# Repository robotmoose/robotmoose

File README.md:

# RobotMoose Web Robotics System

This is a simple, modern version of a networked robotics stack, built around the modern web.  The major pieces are:

* A web **front end** for user friendly robot setup, teleoperation, and programming.  See www/js for the code, which is built in JavaScript on bootstrap.
* A central JSON server called **superstar**, used by the robot to make its sensor values available to the front end (as /superstar/*robotname*/sensors), used the by the front end to post robot commands (at /superstar/*robotname*/robots), and used for persistent storage as well.  See superstar/ for the code, which is built in C++ on Mongoose, but the HTTP get and set commands can be sent from any language, and is conceptually similar to MongoDB.
* An on-robot **back end**, that relays superstar commands to the robot hardware, and keeps track of the robot location.  See tabula_rasa/chromeapp for an easy to use RobotMoose chrome app GUI; or tabula_rasa/ for a command line C++ backend.
* A runtime configurable Arduino **firmware**, which allows new robot hardware to be added at runtime without re-flashing or editing the code.

The typical usage model puts the front end on the robot pilot's web browser, superstar on a cloud server accessible from anywhere, the backend on a laptop onboard the robot, and the Arduino directly wired into the robot hardware.  But you can run all the software on a single low-end laptop for a network-free version, or use a dedicated superstar on a closed network, or many other permutations.

## Installation and Setup

To get started with a simulated robot, just visit [robotmoose.com/robots/](https://robotmoose.com/robots/), and click the "Simulate a Robot" button. This will let you get a general sense of how the website works.

### Firmware Installation and Physical Backend

You need [Google Chrome](https://www.google.com/chrome/browser/desktop/index.html) to run the backend, the version control system git to get this code, and the Arduino IDE to flash the Arduino firmware.

Windows:
* [Git for Windows](https://msysgit.github.io/)
* [Arduino IDE](https://www.arduino.cc/en/Main/Software)

macOS:
* [GitHub for Mac](https://desktop.github.com/)
* [Arduino IDE](https://www.arduino.cc/en/Main/Software)

Ubuntu:
* Terminal command: `sudo apt-get install git arduino`

Now open Terminal (macOS/Ubuntu) or Command Prompt (Windows), and run this command to download the code:

    git clone https://github.com/robotmoose/robotmoose

On Ubuntu, you'll need to run this command to give yourself access to serial devices:

    sudo usermod -a -G dialout $USER

You'll need to log out and log back in to be in the new group.

Now plug in the Arduino and open the Arduino IDE. Open the project at `robotmoose/tabula_rasa/arduino/arduino.ino`, and click the upload button.

You can double check the installation by opening the Arduino as a serial port at 57600 baud. You should get a welcome message.

Open Chrome, and [install the backend app](https://chrome.google.com/webstore/detail/robotmoose/ecadjbcmgjcekpogchpochjieaimpegf?hl=en). Open the backend app, enter your year/school/robot info, and click connect.

You can now use the web interface to configure and pilot your robot!

### Configure and Pilot your Robot with the Web Front End

You access the main robot web interface at [http://robotmoose.com/robots/](http://robotmoose.com/robots/).  
* Connect to the school ("test") and robot name ("yourbot") you gave the backend above.
* Configure the robot in the "Configure" tab by selecting a piece of hardware and hitting "Add".  I always start with a "heartbeat" so I can verify communication works.  Hit "Configure" to copy this configuration to the Arduino.
* Check the "Sensors" tab to see the data sent back by your robot.  The "heartbeat" is a number that counts up from 0 to 255 again and again, so you can see the Arduino is connected.  The "location" is a guess of the position of the robot, and is updated as the robot moves.

There are many options for robot driving hardware (tabula_rasa/arduino/motor_controller.cpp) supported by this system.  Once you configure any of these robot motors, the "Drive" tab will gain a set of arrows allowing you to drive the robot!
* "create2" is a serial connection to an iRobot Create 2 or 500/600 series Roomba.  Arduino Pin 2 should be wired into the serial port wakeup line (otherwise when you press "Configure", you may need to press the Roomba's power button to wake up the Roomba, or the Arduino will sit waiting for the Roomba to connect).
* "bts" represents two BTS 7960B motor controllers, used to drive the left and right wheels of your robot.  There are four pins listed, two PWM pins for each motor.  (Tie the BTS's VCC and EN lines to Arduino 5V, and the GND line to Arduino ground.  You can leave the IS pins unconnected.)
* "sabertooth2" is a Dimension Engineering SaberTooth dual motor controller, version 2.  You set the serial port that sends serial commands to this device.  (Set address 128, packetized serial format, 9600 baud)
* "sabertooth1" is a Dimension Engineering SaberTooth, version 1.  (Set simple serial format, 9600 baud)

There are also several robot peripherals supported:
* "pwm" is a pulse width modulated (PWM) pin, which can be used to smoothly vary the brightness of an LED.  For example, pin 13 is the standard Arduino LED, so you can control it by adding a pwm device on pin 13, and dragging the brightness slider around.  This is a good first project to try!
* "servo" is an RC servo, like with a model plane.  You can hook the servo's white control wire to any Arduino pin, and power the red from 5v and black to ground.  In the "Drive" tab, you set the servo position in degrees, from 0 to 180 degrees.
* "analog" reads an Arduino analog pin, like A3.  The read value will show up in the Sensors tab.
* "neato" is a Neato XV-11 laser distance sensor, which uses a laser to measure distance in a 360 degree plane around the robot.  You give a serial port to read the neato's serial data distance reports, and a pin to control the neato's motor power via a transistor.
* "latency" measures the Arduino firmware's control loop latency, in milliseconds.  It should normally read 1 millisecond.
* "heartbeat" is incremented every 10ms by Arduino firmware.  If you can see this number changing in the "Sensors" tab, you have connectivity between the web front end, superstar, backend, and Arduino.  If this number stops changing, something has been disconnected.

### Making a Superstar
For most tasks, it's best to use UAF's main superstar server (http://robotmoose.com/superstar/).  But if you don't have reliable internet access, or want to change our web user interface code, you need your own local superstar server. These instructions assume you're running macOS or Ubuntu, with basic dev tools installed.

To make and run your own local copy of superstar:
```
cd ~/robotmoose/superstarv2
make
./superstar > log &
```  

When you first start your superstar, you will not have an admin password, or have any robots. You will need to create them by using the superstar utility programs:
```
cd ~/robotmoose/utils/superstarv2
./starpasswd.py -s localhost:8081
./make_robot.py -s localhost:8081  2018/testschool/testbot
```
That starpasswd command creates an admin password.

That make_robot command creates a robot named "testbot" at "testschool".

(If you have password problems, the password paths and hashes are stored in a plain text file named "robotmoose/superstarv2/auth".)

Start a robot backend and connect it to this local interface by changing the "robotmoose.com" dropdown to "127.0.0.1:8081".

You should now be able to point your web browser to [http://localhost:8081/robots/](http://localhost:8081/robots/) and see your local copy of the web user interface.  Edit the files in ~/robotmoose/www/js and hit reload to modify the interface.  You can also manually examine the entries in [http://localhost:8081/superstar/](http://localhost:8081/superstar/) to see how the robot configuration, sensor, and pilot information is exchanged, using superstar get and set operations.

Using the entire robotmoose system on your local network, with robots on different machines accessing your local superstar, requires a few extra steps:
* First, you must note the local IP address of the machine running your local superstar (for example, "192.168.1.24").
* Next, you must add this IP address to the Chrome App:
    * First, open up [tabula_rasa/chromeapp/manifest.json](tabula_rasa/chromeapp/manifest.json). To the permissions array, add the IP address of your local superstar, making sure to add "http" and port "8081" (e.g., "http://192.168.1.24:8081"). Mind the commas in the array!
    * Then, in [tabula_rasa/chromeapp/js/src/name.js](tabula_rasa/chromeapp/js/src/name.js), search for the `update_superstars_m` function. In the `superstar_options` array, add the IP address and port number of your local superstar (e.g. "192.168.1.24:8081").
* Finally, you must load the modified chrome app onto all of the backend computers:
    * Copy the modified chromeapp folder [tabula_rasa/chromeapp](tabula_rasa/chromeapp) and its files to the backend computer(s).
    * Go to [chrome://extensions/](chrome://extensions/), click the developer mode checkbox. If you have already loaded the chrome app from the git before, you will have to remove it because of the changes to manifest.json.
    * Click "load unpacked extension", browse to the chromeapp folder, then click ok.
    * When you launch the chrome app, the IP of your local superstar should appear in the backend dropdown!

### Fun Tricks
The superstar server has been tested with up to ten robots and pilots connected.  Normally, each robot has a unique name, which allows the pilot to control it.

If you give several robots the same name, the pilot interface jumps between their sensor data as they report it, which isn't very useful.  But all the robots read the same pilot commands, so they move together like synchronized swimmers!

If several pilots connect to the same robot, they all see the same sensor data, but the pilot's commands overwrite each other, which makes for very jerky driving.

## Debugging
The real trick with debugging is slowly and systematically looking at what is happening.

### Problem: Arduino permission error
If you have an Arduino permission problem, flashing the Arduino from the command line (cd ~/robotmoose/tabula_rasa/arduino; make) will error with:
```
avrdude: ser_open(): can't open device "/dev/ttyACM0": Permission denied
ioctl("TIOCMGET"): Invalid argument
ioctl("TIOCMGET"): Invalid argument
```

Even if you manage to flash the Arduino, if you have a permission problem the backend will hang when connecting to the Arduino:
```
Uploading new config to arduino!
Arduino startup:
```

A temporary fix is to force the Arduino device to be readable and writeable, but this will need to be repeated every time you unplug the Arduino:
```
sudo chmod 777 /dev/tty[UA]*
```

The permanent fix for both problems is to make all serial devices readable and writeable by your user account:
```
sudo usermod -a -G dialout $USER
```
You'll need to log out and log back in to be in the new group, and then any Arduino should work correctly, permanently.

### Problem: Internet Connection Error
The backend needs a network connection to the superstar server, or you will get errors like this:
```
Connecting to superstar at http://robotmoose.com/
terminate called after throwing an instance of 'skt_error'
  what():  Invalid domain name: 'robotmoose.com'
```

Check that the wireless network is connected correctly.  Can you reach google from the backend laptop?

### Problem: Robot does not drive
Things to look at:
* Are you getting a heartbeat in the "Sensors" tab?  If no heartbeat is listed, configure one.  If the heartbeat is shown but not counting, the problem is either the backend or the Arduino.  Is the backend laptop running, and does it have internet?  Is the backend running, and does it display any error messages?  Is the Arduino plugged in?
* Is the Roomba running?  If the heartbeat is running but the "light" sensors are not changing, you may need to go to the "Configure" tab and hit Configure again to restart the Roomba.  Also check the Roomba battery in the "Sensor" tab; a Roomba with a low battery will not drive.

### Problem: Superstar compilation fails with "Missing dependency operator"
If you get an error similar to this when you try to `make` Superstar:

	make: "/usr/home/christopher/Code/robotmoose/superstar/Makefile" line 7: Missing dependency operator
	make: "/usr/home/christopher/Code/robotmoose/superstar/Makefile" line 9: Need an operator
	make: Fatal errors encountered -- cannot continue
	make: stopped in /usr/home/christopher/Code/robotmoose/superstar

The problem is that Superstar's `Makefile` uses GNU make-specific features. To solve the problem, install `gmake` on your system (if it's not installed already), then run `gmake` instead of `make`.

## Project Background

This is an NSF-funded ITEST research project, with full name:
Collaborative Research: ITEST-Strategies: Human-Centered Robotics Experiences for Exploring Engineering, Computer Science, and Society

* Seta Bogosyan <sbogosyan@alaska.edu>, PI
* Orion Lawlor <lawlor@alaska.edu>, Co-PI
* Cindy Hmelo-Silver <chmelosi@gmail.com>, Co-PI
* Selma Sabanovic <selmas@indiana.edu>, Co-PI

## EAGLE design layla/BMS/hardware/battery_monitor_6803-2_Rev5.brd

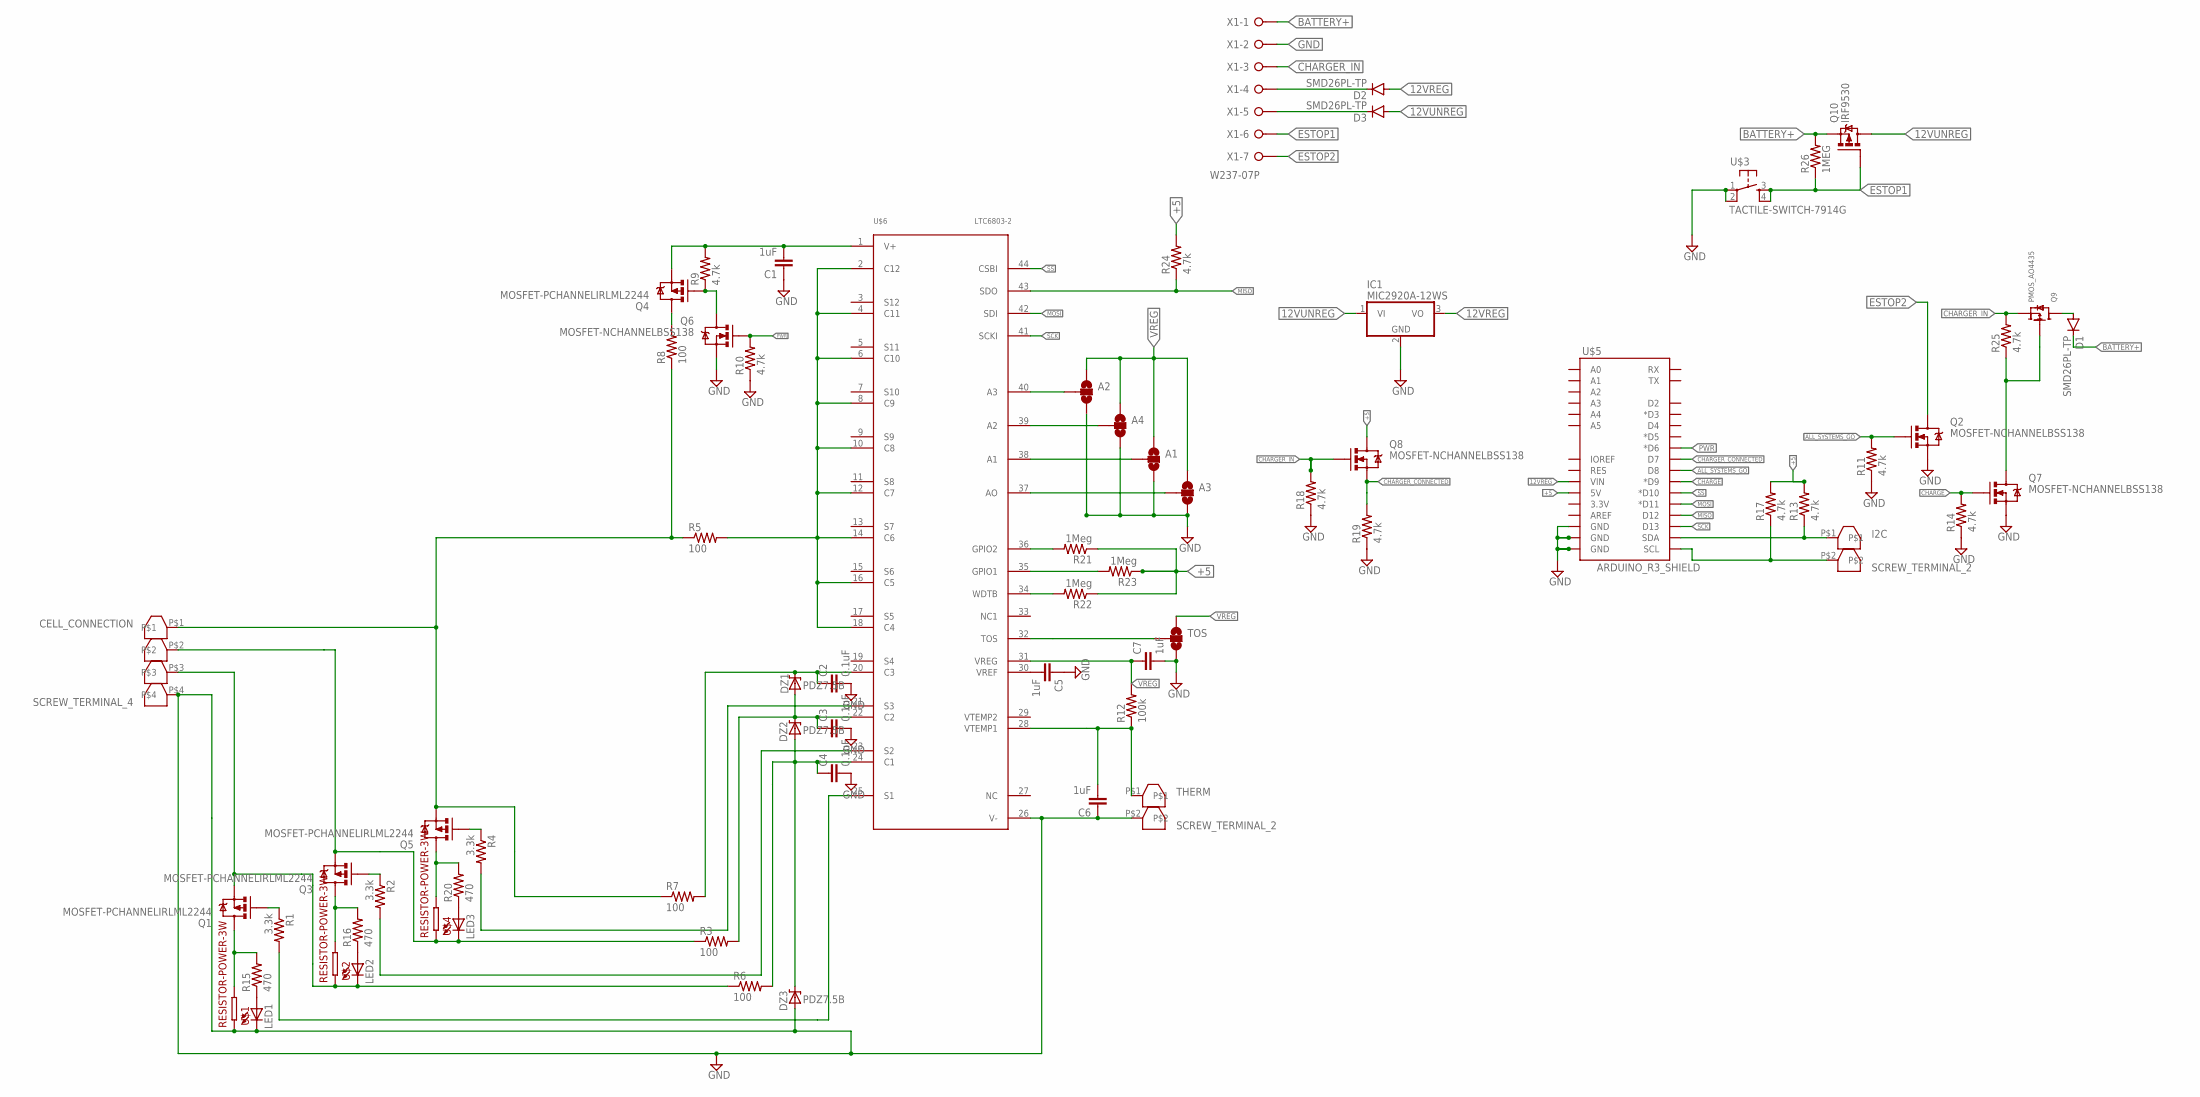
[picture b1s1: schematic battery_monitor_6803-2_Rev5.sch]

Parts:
A1, A2, A3, A4: SOLDERJUMPER_2WAYS; SJ_3
C1, C5, C6, C7: 1uF; 0603-CAP; MPN C0603X5R0J105M030BC
C2, C3, C4: 0.1uF; 0603-CAP; MPN 0603YG104ZAT2A
CELL_CONNECTION: SCREW_TERMINAL_4; MPN 282834-4
D1, D2, D3: SMD26PL-TP; SOD-123
DZ1, DZ2, DZ3: PDZ7.5B; SOD-323@1; MPN PDZ7.5B,115
I2C: SCREW_TERMINAL_2; MPN 282834-2
IC1: MIC2920A-12WS; SOT223
LED1, LED2, LED3: LED0603; LED-0603; MPN 150060RS75000
Q1, Q3, Q4, Q5: MOSFET-PCHANNELIRLML2244; SOT23-3@1; MPN SI2369DS-T1-GE3
Q2, Q6, Q7, Q8: MOSFET-NCHANNELBSS138; SOT23; MPN IRLML0030TRPBF
Q9: PMOS_AO4435; SOIC8; MPN SI9407BDY-T1-GE3
Q10: IRF9530; TO220BV; MPN NTE2383
R1, R2, R4: 3.3k; 0603-RES; MPN CRCW06033K00FKEA
R3, R5, R6, R7, R8: 100; 0603-RES; MPN ERJ-1GNF1000C
R9, R10, R11, R13, R14, R17, R18, R19, R24, R25: 4.7k; 0603-RES; MPN CRCW06034K70FKEA
R12: 100k; 0603-RES; MPN MC0063W06035100K
R15, R16, R20: 470; 0603-RES; MPN ERJ-P03F4700V
R21, R22, R23: 1Meg; 0603-RES; MPN ERJ-3EKF1004V
R26: 1MEG; 0603-RES; MPN ERJ-3EKF1004V
THERM: SCREW_TERMINAL_2; MPN 282834-2
TOS: SOLDERJUMPER_2WAYS; SJ_3
U$1, U$2, U$4: RESISTOR-POWER-3W; RESISTOR-3W; MPN ERG-3SJ200
U$3: TACTILE-SWITCH-7914G; 7914G; MPN 7914G-1-000E
U$5: ARDUINO_R3_SHIELD; UNO_R3_SHIELD
U$6: LTC6803-2; FSOP-44
X1: W237-07P; W237-7P

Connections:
12VREG: D2.A, IC1.3 (VO), U$5.VIN
12VUNREG: D3.A, IC1.1 (VI), Q10.D
+5: Q8.3 (D), R13.2, R17.2, R21.1, R22.1, R23.1, R24.2, U$5.5V
ALL_SYSTEMS_GO: Q2.1 (G), R11.2, U$5.D8
BATTERY+: D1.C, Q10.S, R26.2, X1.1
CHARGE: Q7.1 (G), R14.2, U$5.D9 (*D9)
CHARGER_CONNECTED: Q8.2 (S), R19.2, U$5.D7
CHARGER_IN: Q8.1 (G), Q9.1 (SOURCE), Q9.2 (SOURCE), Q9.3 (SOURCE), R18.2, R25.2, X1.3
ESTOP1: Q10.G, R26.1, U$3.3, U$3.4, X1.6
ESTOP2: Q2.3 (D), X1.7
GND: A1.3, A2.3, A3.3, A4.3, C1.1, C2.2, C3.2, C4.2, C5.1, C6.1, C7.2, CELL_CONNECTION.P$4, DZ3.2 (A), IC1.2 (GND), LED1.C, Q2.2 (S), Q6.2 (S), Q7.2 (S), R10.1, R11.1, R14.1, R18.1, R19.1, THERM.P$2, TOS.3, U$1.P$2, U$3.1, U$3.2, U$5.GND@0 (GND), U$5.GND@1 (GND), U$5.GND@2 (GND), U$6.26 (V-), X1.2
MISO: R24.1, U$5.D12, U$6.43 (SDO)
MOSI: U$5.D11 (*D11), U$6.42 (SDI)
unnamed: Q7.3 (D), Q9.4 (GATE), R25.1
unnamed: CELL_CONNECTION.P$3, LED2.C, Q1.2 (S), R6.1, U$2.P$2
unnamed: CELL_CONNECTION.P$2, LED3.C, Q3.2 (S), R3.1, U$4.P$2
unnamed: CELL_CONNECTION.P$1, Q5.2 (S), R5.1, R7.1, R8.1
unnamed: Q1.3 (D), R15.2, U$1.P$1
unnamed: R2.2, U$6.23 (S2)
unnamed: Q1.1 (G), R1.1
unnamed: R1.2, U$6.25 (S1)
unnamed: R4.2, U$6.21 (S3)
unnamed: Q3.3 (D), R16.2, U$2.P$1
unnamed: Q3.1 (G), R2.1
unnamed: Q5.3 (D), R20.2, U$4.P$1
unnamed: LED1.A, R15.1
unnamed: C2.1, DZ1.1 (C), R7.2, U$6.20 (C3)
unnamed: C4.1, DZ2.2 (A), DZ3.1 (C), R6.2, U$6.24 (C1)
unnamed: C3.1, DZ1.2 (A), DZ2.1 (C), R3.2, U$6.22 (C2)
unnamed: R5.2, U$6.2 (C12), U$6.4 (C11), U$6.6 (C10), U$6.8 (C9), U$6.10 (C8), U$6.12 (C7), U$6.14 (C6), U$6.16 (C5), U$6.18 (C4)
unnamed: Q4.3 (D), R8.2
unnamed: C1.2, Q4.2 (S), R9.2, U$6.1 (V+)
unnamed: Q4.1 (G), Q6.3 (D), R9.1
unnamed: C6.2, R12.1, THERM.P$1, U$6.28 (VTEMP1)
unnamed: LED2.A, R16.1
unnamed: LED3.A, R20.1
unnamed: R21.2, U$6.36 (GPIO2)
unnamed: R23.2, U$6.35 (GPIO1)
unnamed: D3.C, X1.5
unnamed: R22.2, U$6.34 (WDTB)
unnamed: A2.2, U$6.40 (A3)
unnamed: Q5.1 (G), R4.1
unnamed: A4.2, U$6.39 (A2)
unnamed: A1.2, U$6.38 (A1)
unnamed: A3.2, U$6.37 (AO)
unnamed: TOS.2, U$6.32 (TOS)
unnamed: C5.2, U$6.30 (VREF)
N$$8: D1.A, Q9.5 (DRAIN), Q9.6 (DRAIN), Q9.7 (DRAIN), Q9.8 (DRAIN)
PWR: Q6.1 (G), R10.2, U$5.D6 (*D6)
SCK: U$5.D13, U$6.41 (SCKI)
SCL: I2C.P$2, R17.1, U$5.SCL
SDA: I2C.P$1, R13.1, U$5.SDA
SS: U$5.D10 (*D10), U$6.44 (CSBI)
VREG: A1.1, A2.1, A3.1, A4.1, C7.1, R12.2, TOS.1, U$6.31 (VREG)
WIRE: D2.C, X1.4

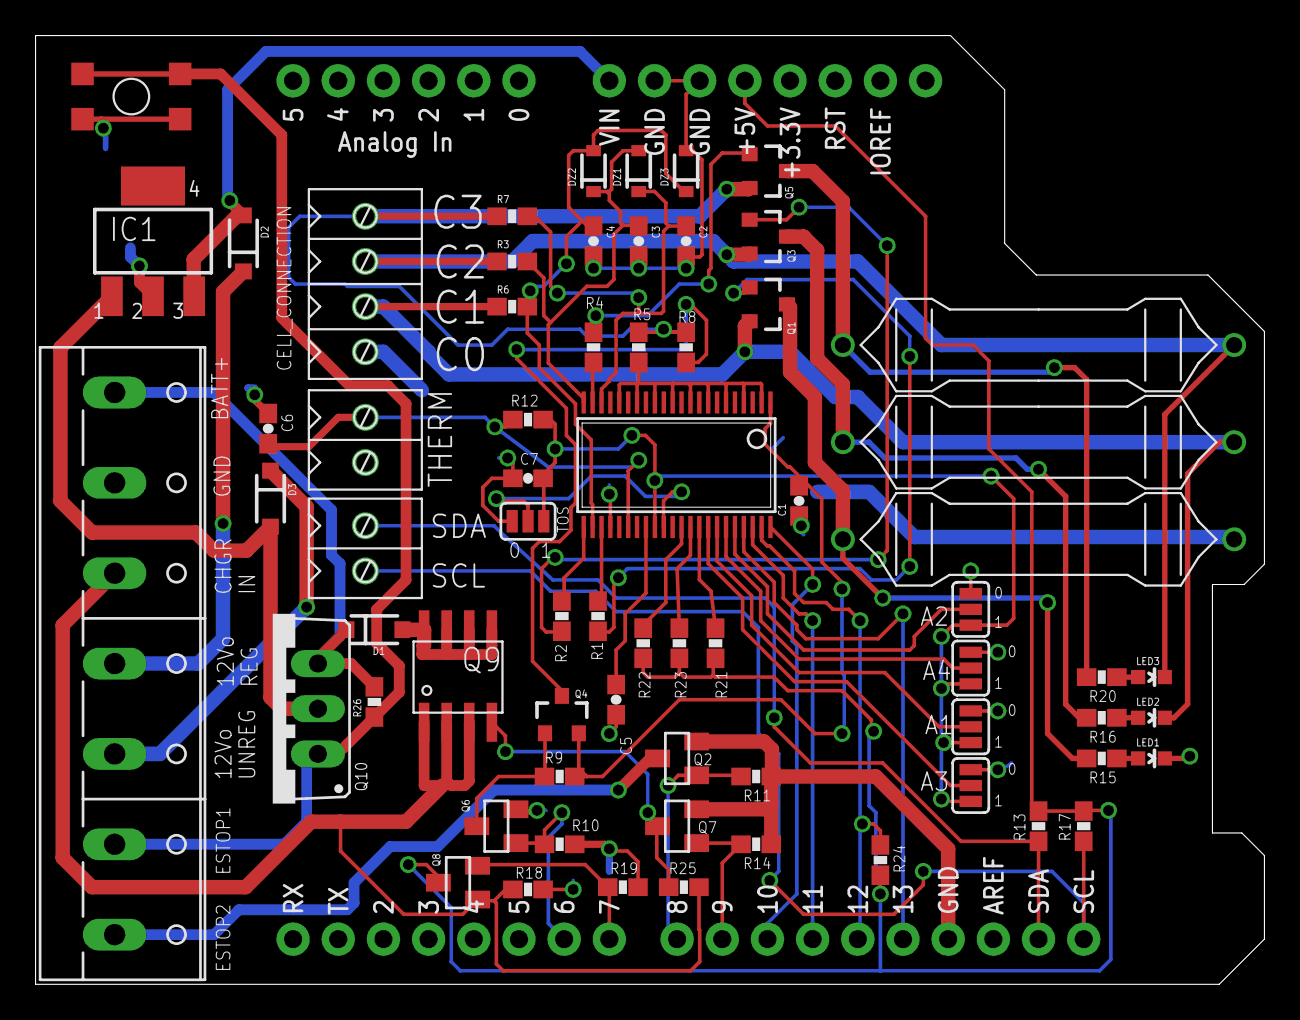
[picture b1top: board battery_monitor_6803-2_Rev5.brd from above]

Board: 2 copper layers, 69.1 x 53.3 mm, 68 parts (0 on the bottom side), 55 nets.

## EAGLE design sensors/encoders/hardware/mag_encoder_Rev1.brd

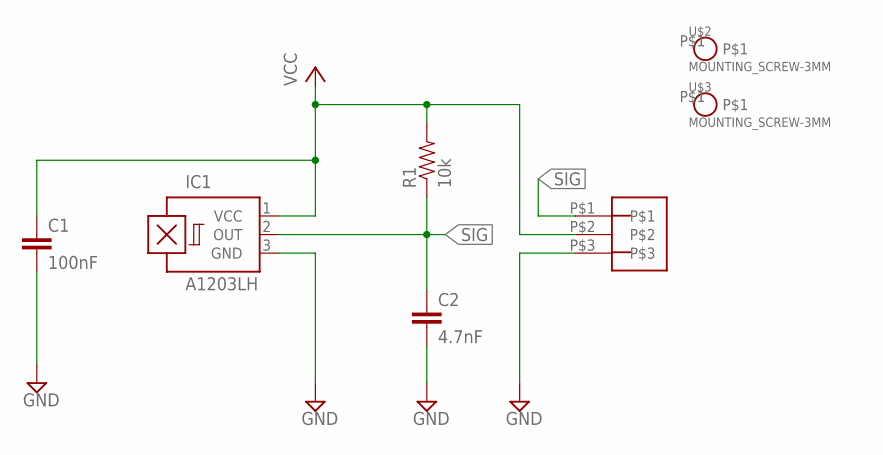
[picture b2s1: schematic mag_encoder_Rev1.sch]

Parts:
C1: 100nF; 0603-CAP
C2: 4.7nF; 0603-CAP
IC1: A1203LH; SOT23-W
R1: 10k; 0603
U$1: 3_PIN_JST-XH
U$2, U$3: MOUNTING_SCREW-3MM

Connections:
GND: C1.2, C2.2, IC1.3 (GND), U$1.P$3
SIG: C2.1, IC1.2 (OUT), R1.1, U$1.P$1
VCC: C1.1, IC1.1 (VCC), R1.2, U$1.P$2

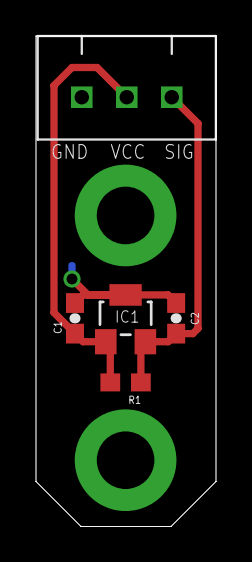
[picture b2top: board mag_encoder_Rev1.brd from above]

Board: 2 copper layers, 10.0 x 27.2 mm, 7 parts (0 on the bottom side), 3 nets.

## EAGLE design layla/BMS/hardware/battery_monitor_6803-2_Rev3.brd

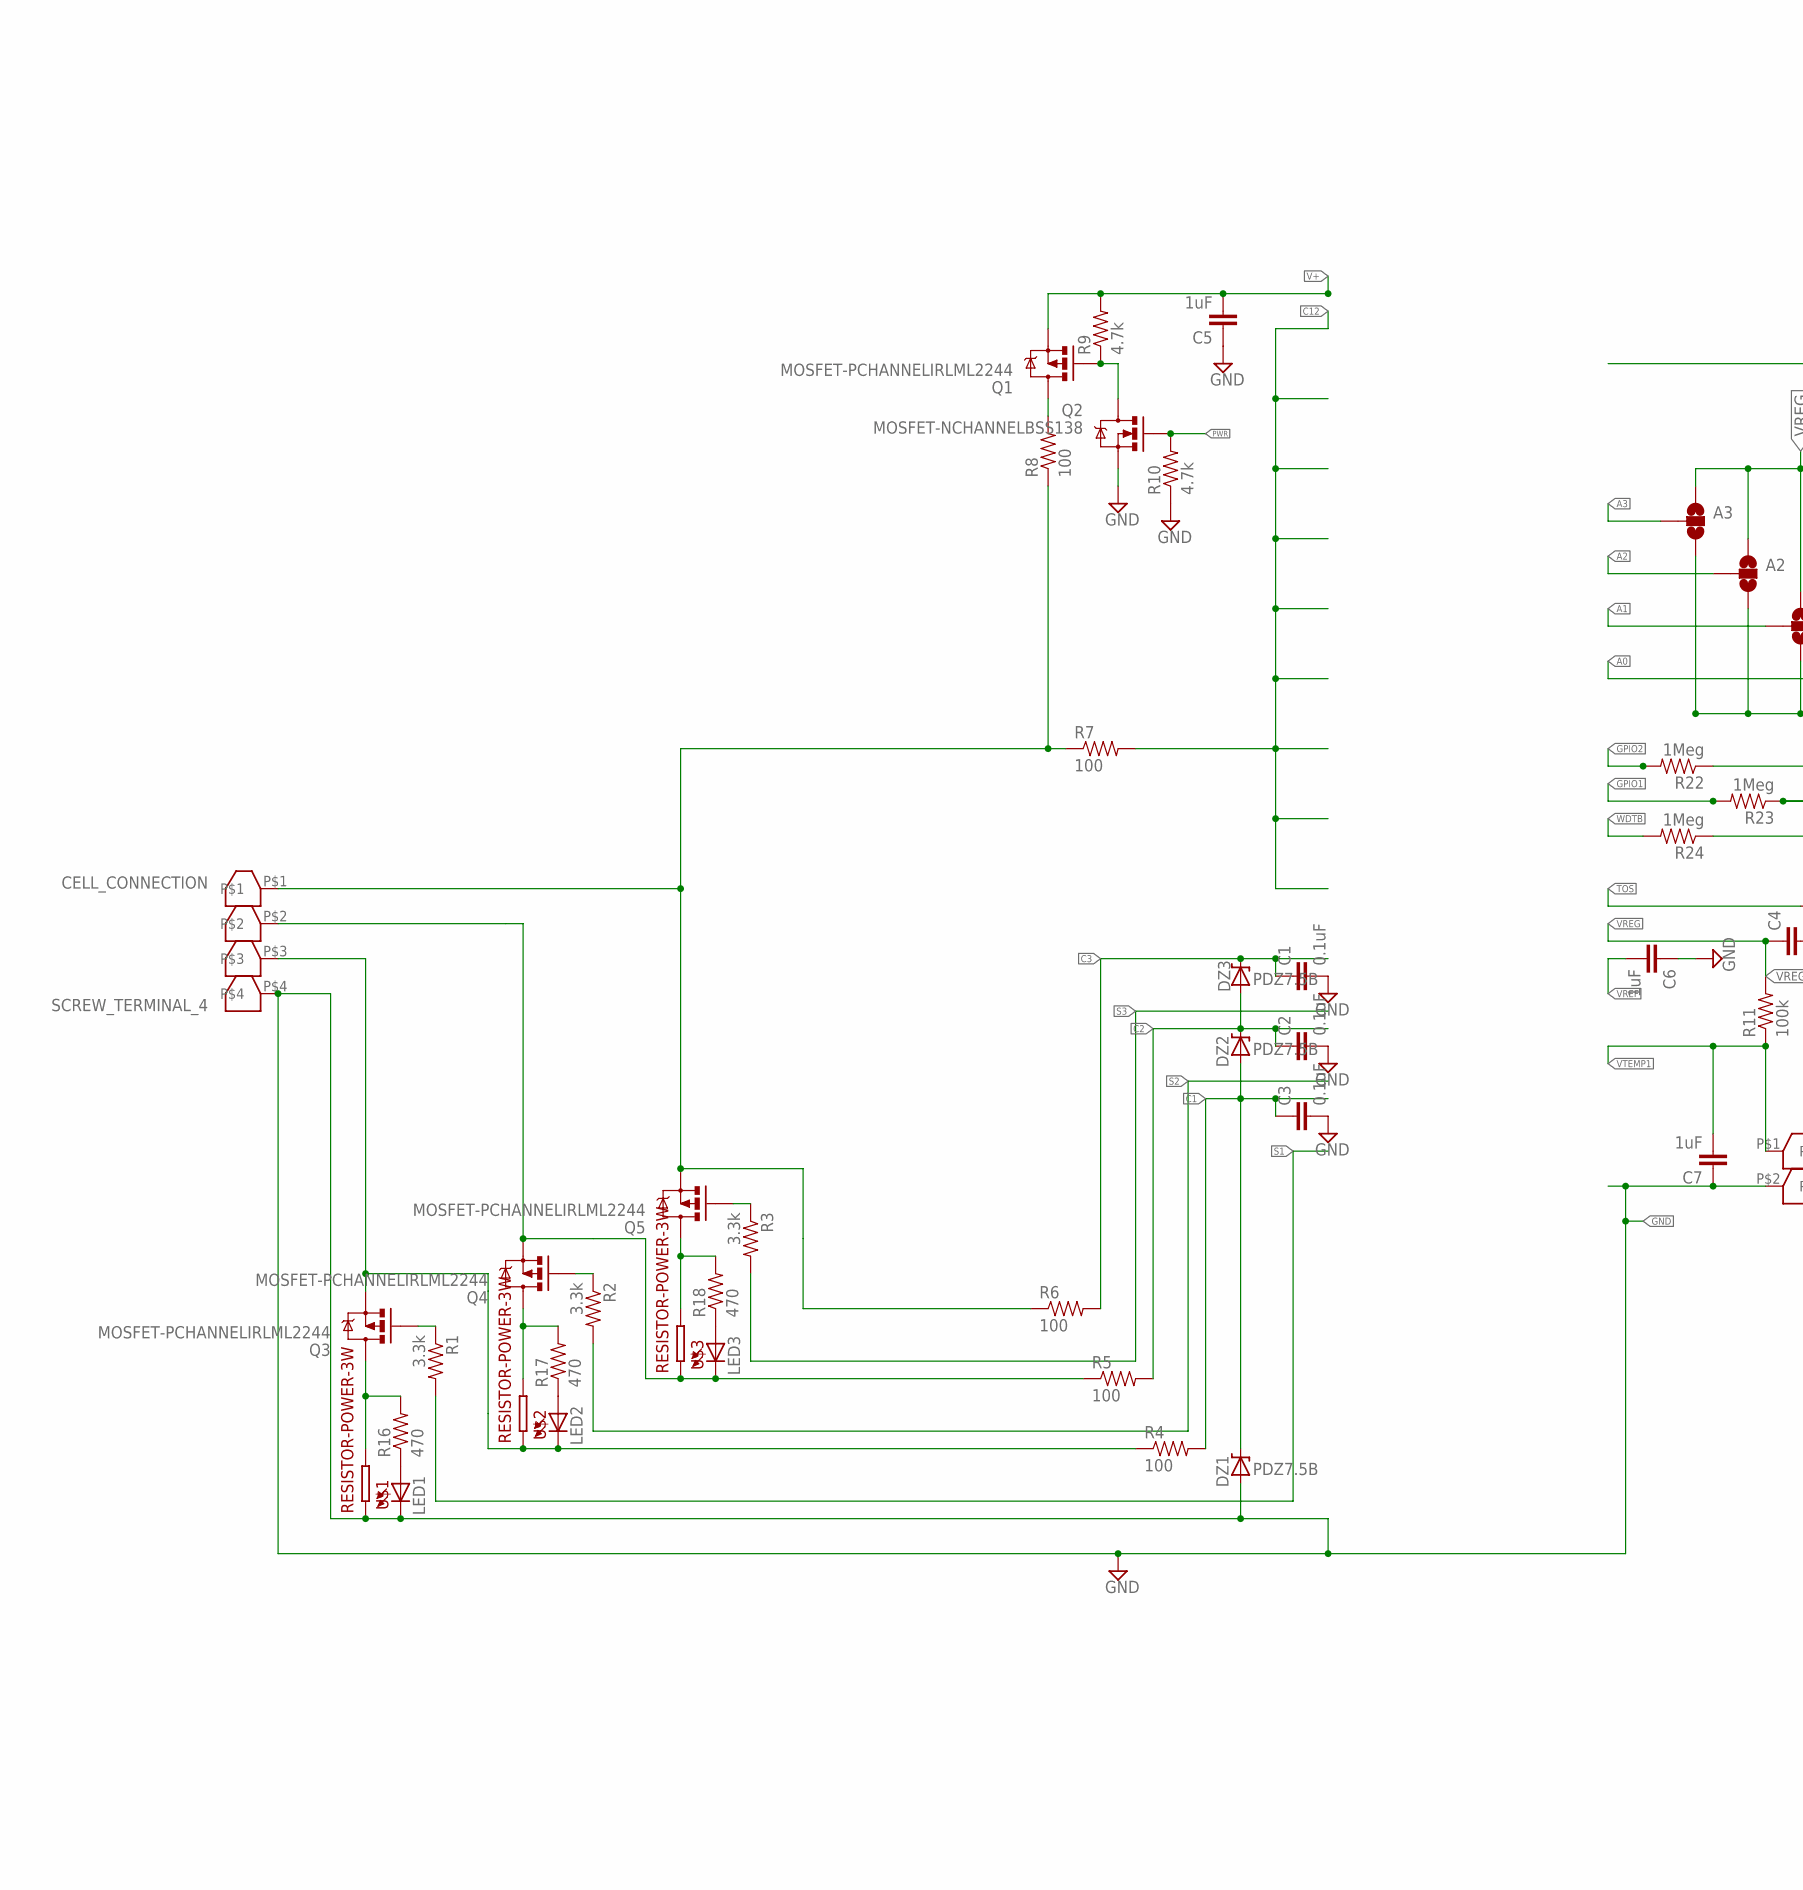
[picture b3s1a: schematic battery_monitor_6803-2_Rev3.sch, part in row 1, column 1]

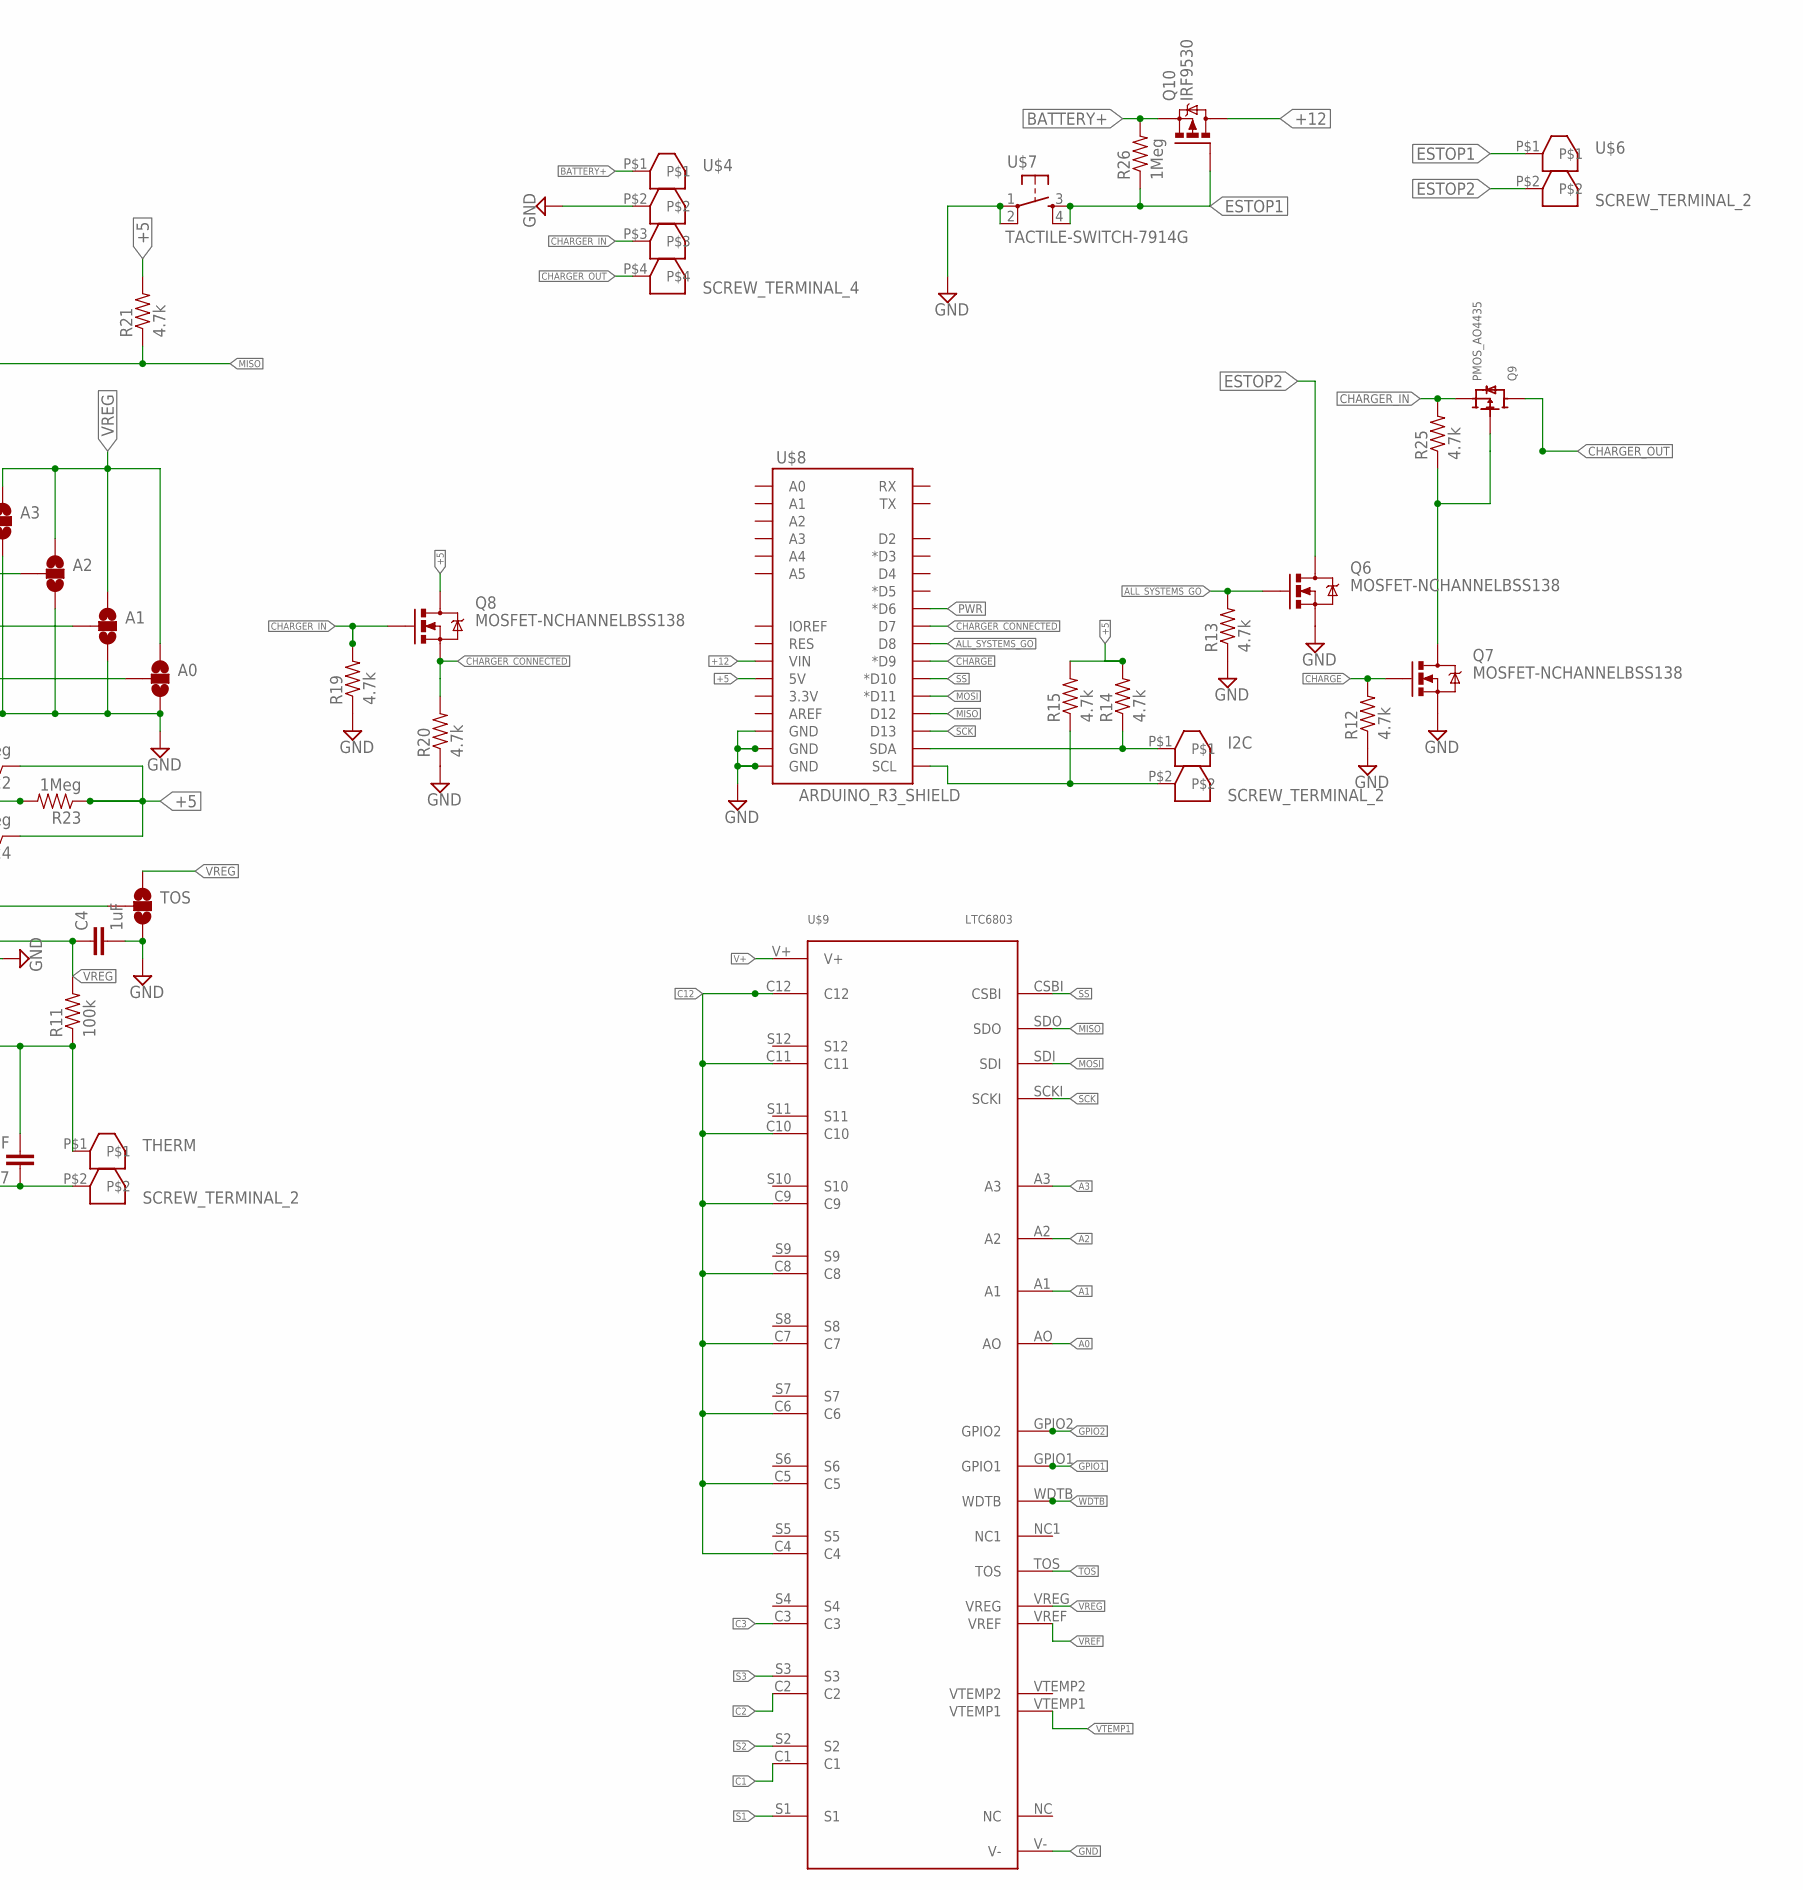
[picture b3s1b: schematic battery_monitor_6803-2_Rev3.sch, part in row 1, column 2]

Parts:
A0, A1, A2, A3: SOLDERJUMPER_2WAYS; SJ_3
C1, C2, C3: 0.1uF; 0603-CAP; MPN 0603YG104ZAT2A
C4, C5, C6, C7: 1uF; 0603-CAP; MPN C0603X5R0J105M030BC
CELL_CONNECTION: SCREW_TERMINAL_4; MPN 282834-4
DZ1, DZ2, DZ3: PDZ7.5B; SOD-323; MPN PDZ7.5B,115
I2C: SCREW_TERMINAL_2; MPN 282834-2
LED1, LED2, LED3: LED0603; LED-0603; MPN 150060RS75000
Q1, Q3, Q4, Q5: MOSFET-PCHANNELIRLML2244; SOT23-3; MPN IRLML2244TRPBF
Q2, Q6, Q7, Q8: MOSFET-NCHANNELBSS138; SOT23; MPN IRLML0030TRPBF
Q9: PMOS_AO4435; SOIC8; MPN SI9407BDY-T1-GE3
Q10: IRF9530; TO220BV; MPN NTE2383
R1, R2, R3: 3.3k; 0603-RES; MPN CRCW06033K00FKEA
R4, R5, R6, R7, R8: 100; 0603-RES; MPN ERJ-1GNF1000C
R9, R10, R12, R13, R14, R15, R19, R20, R21, R25: 4.7k; 0603-RES; MPN CRCW06034K70FKEA
R11: 100k; 0603-RES; MPN MC0063W06035100K
R16, R17, R18: 470; 0603-RES; MPN ERJ-P03F4700V
R22, R23, R24, R26: 1Meg; 0603-RES; MPN ERJ-3EKF1004V
THERM: SCREW_TERMINAL_2; MPN 282834-2
TOS: SOLDERJUMPER_2WAYS; SJ_3
U$1, U$2, U$3: RESISTOR-POWER-3W; RESISTOR-3W; MPN ERG-3SJ200
U$4: SCREW_TERMINAL_4; MPN 282834-4
U$6: SCREW_TERMINAL_2; MPN 282834-2
U$7: TACTILE-SWITCH-7914G; 7914G; MPN 7914G-1-000E
U$8: ARDUINO_R3_SHIELD; UNO_R3_SHIELD
U$9: LTC6803; LTC6803_BREAKOUT; MPN LTC6803IG-2#PBF

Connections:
+5: Q8.3 (D), R14.2, R15.2, R21.2, R22.1, R23.1, R24.1, U$8.5V
+12: Q10.D, U$8.VIN
A0: A0.2, U$9.AO
A1: A1.2, U$9.A1
A2: A2.2, U$9.A2
A3: A3.2, U$9.A3
ALL_SYSTEMS_GO: Q6.1 (G), R13.2, U$8.D8
BATTERY+: Q10.S, R26.2, U$4.P$1
C1: C3.1, DZ1.1 (C), DZ2.2 (A), R4.2, U$9.C1
C2: C2.1, DZ2.1 (C), DZ3.2 (A), R5.2, U$9.C2
C3: C1.1, DZ3.1 (C), R6.2, U$9.C3
C12: R7.2, U$9.C4, U$9.C5, U$9.C6, U$9.C7, U$9.C8, U$9.C9, U$9.C10, U$9.C11, U$9.C12
CHARGE: Q7.1 (G), R12.2, U$8.D9 (*D9)
CHARGER_CONNECTED: Q8.2 (S), R20.2, U$8.D7
CHARGER_IN: Q8.1 (G), Q9.1 (SOURCE), Q9.2 (SOURCE), Q9.3 (SOURCE), R19.2, R25.2, U$4.P$3
CHARGER_OUT: Q9.5 (DRAIN), Q9.6 (DRAIN), Q9.7 (DRAIN), Q9.8 (DRAIN), U$4.P$4
ESTOP1: Q10.G, R26.1, U$6.P$1, U$7.3, U$7.4
ESTOP2: Q6.3 (D), U$6.P$2
GND: A0.3, A1.3, A2.3, A3.3, C1.2, C2.2, C3.2, C4.2, C5.1, C6.1, C7.1, CELL_CONNECTION.P$4, DZ1.2 (A), LED1.C, Q2.2 (S), Q6.2 (S), Q7.2 (S), R10.1, R12.1, R13.1, R19.1, R20.1, THERM.P$2, TOS.3, U$1.P$2, U$4.P$2, U$7.1, U$7.2, U$8.GND@0 (GND), U$8.GND@1 (GND), U$8.GND@2 (GND), U$9.V-
GPIO1: R23.2, U$9.GPIO1
GPIO2: R22.2, U$9.GPIO2
MISO: R21.1, U$8.D12, U$9.SDO
MOSI: U$8.D11 (*D11), U$9.SDI
unnamed: Q7.3 (D), Q9.4 (GATE), R25.1
unnamed: CELL_CONNECTION.P$3, LED2.C, Q3.2 (S), R4.1, U$2.P$2
unnamed: CELL_CONNECTION.P$2, LED3.C, Q4.2 (S), R5.1, U$3.P$2
unnamed: CELL_CONNECTION.P$1, Q5.2 (S), R6.1, R7.1, R8.1
unnamed: Q3.3 (D), R16.2, U$1.P$1
unnamed: Q3.1 (G), R1.1
unnamed: Q4.3 (D), R17.2, U$2.P$1
unnamed: Q4.1 (G), R2.1
unnamed: Q5.3 (D), R18.2, U$3.P$1
unnamed: LED1.A, R16.1
unnamed: Q1.3 (D), R8.2
unnamed: Q1.1 (G), Q2.3 (D), R9.1
unnamed: LED2.A, R17.1
unnamed: LED3.A, R18.1
unnamed: Q5.1 (G), R3.1
PWR: Q2.1 (G), R10.2, U$8.D6 (*D6)
S1: R1.2, U$9.S1
S2: R2.2, U$9.S2
S3: R3.2, U$9.S3
SCK: U$8.D13, U$9.SCKI
SCL: I2C.P$2, R15.1, U$8.SCL
SDA: I2C.P$1, R14.1, U$8.SDA
SS: U$8.D10 (*D10), U$9.CSBI
TOS: TOS.2, U$9.TOS
V+: C5.2, Q1.2 (S), R9.2, U$9.V+
VREF: C6.2, U$9.VREF
VREG: A0.1, A1.1, A2.1, A3.1, C4.1, R11.2, TOS.1, U$9.VREG
VTEMP1: C7.2, R11.1, THERM.P$1, U$9.VTEMP1
WDTB: R24.2, U$9.WDTB

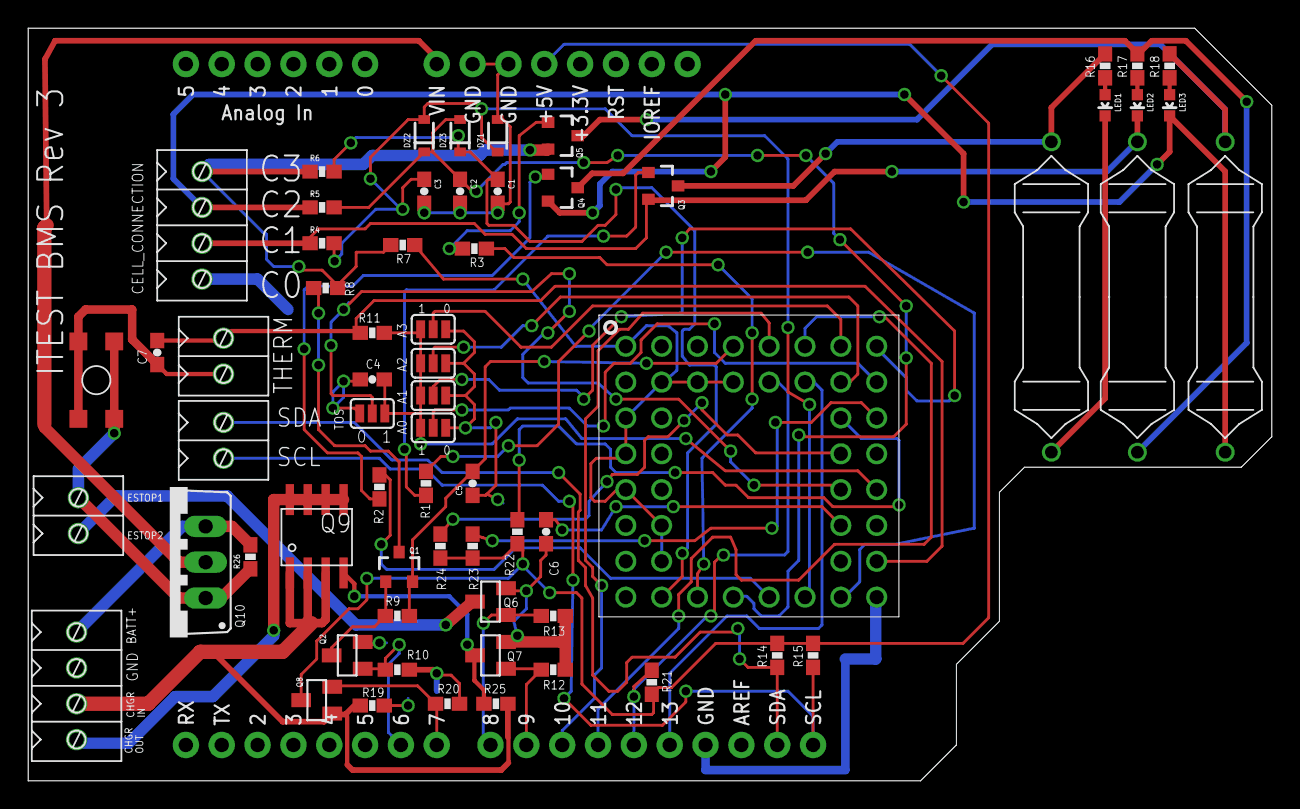
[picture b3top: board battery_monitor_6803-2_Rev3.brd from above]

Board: 2 copper layers, 88.1 x 53.3 mm, 65 parts (0 on the bottom side), 52 nets.

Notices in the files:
parts and their libraries:
SparkFun-DiscreteSemi: Licensing: CC v3.0 Share-Alike You are welcome to use this library for commercial purposes.
GeekAmmo: Licensing:Creative Commons ShareAlike 4.0 International - https://creativecommons.org/licenses/by-sa/4.0
